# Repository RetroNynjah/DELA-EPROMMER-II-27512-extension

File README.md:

# DELA-EPROMMER-II 27512 Extension

## Background 
This is a reproduction of the 27512 extension board from DELA-Elektronik for the DELA-EPROMMER II for the Commodore 64.  
The user instruction calls this add-on "Umbauset für den DELA-EPROMMER II"

This extension makes it possible to program 27512 EPROMS with the DELA-EPROMMER II by removing VPP from pin 1 and replacing it with the switch controlled address pin A15. A special version of the DELA EPROMMER software is needed which connects VPP to pin 22. This special version is available in the software folder.
The 27512 has to be programmed in two 32kB passes and there are two switches on the board, one for activation/deactivation of the extension and one for 32kB block selection (A15).

When this extension is active, the EPROMMER should only be used with a special version of the DELA EPROMMER software. If the extension is deactivated by the switch, it can be used with the standard software.
A scan of the orginal German user manual for the extension was posted in [this forum thread](https://www.forum64.de/index.php?thread/109845-dela-ii-brenner-mit-zusatzplatine/). There's also a copy in the docs folder.

## Installation instruction
Follow the german user instruction in the docs folder or:

* Remove the diode that is located close to the ZIF socket and the LED. That diode is called D1 on Dirk's reproduction PCB.
* Solder points A,B,C,D on the extensions to the four corner pins of the ZIF socket on the bottom side of the board.
* Wire point E on the extension board to where the anode side of the diode was connected. See photos below or the original instruction in the docs folder.

The part count fort this build is low.
The two slide switches in the design are different from the ones on the original extension because silde switches with that pitch can't be found anymore.  
The ones I used are right-angle switches with a 2mm pitch and has solder connections for the metal frame to add stability. I used a cheap TE switch with part number 1825232-1 which can be found at Digikey with part number A107673-ND.  
The diode is a 1N4148.  
The posts that I use to connect the extension to the pins on bottom of the ZIF-socket are four pins that I pulled out of an IC socket with machined (round) pins. They can usually be grabbed with pliers and pushed out of the socket.

## Usage
**Warning!** Activate the exetension only together with the modified software.

The EPROM has to be programmed in two halved because a full 64kB EPROM image can't fit in RAM so you need to split your ROM file in two halves before programming.

To burn a 27512 EPROM:
* Activate the extension by setting the right switch to the ON position.
* Fire up the custom 512kbit version of the EPROMMER-II application
* Insert EPROM to be programmed.
* Load one half of the 64KByte ROM you want to program.
* Use the left slide switch to select which half you want to program
* Go into the EPROM programming menu and program as usual but select the invisible 6th option (27512) when selecting EPROM type.
* Repeat procedure for the next half of the EPROM

Dirk Wouters has created a reproduction of the complete DELA-EPROMMER II which together with schematics, user manuals and standard software can be found at https://github.com/DL2DW/DELA-EPROMMER-II

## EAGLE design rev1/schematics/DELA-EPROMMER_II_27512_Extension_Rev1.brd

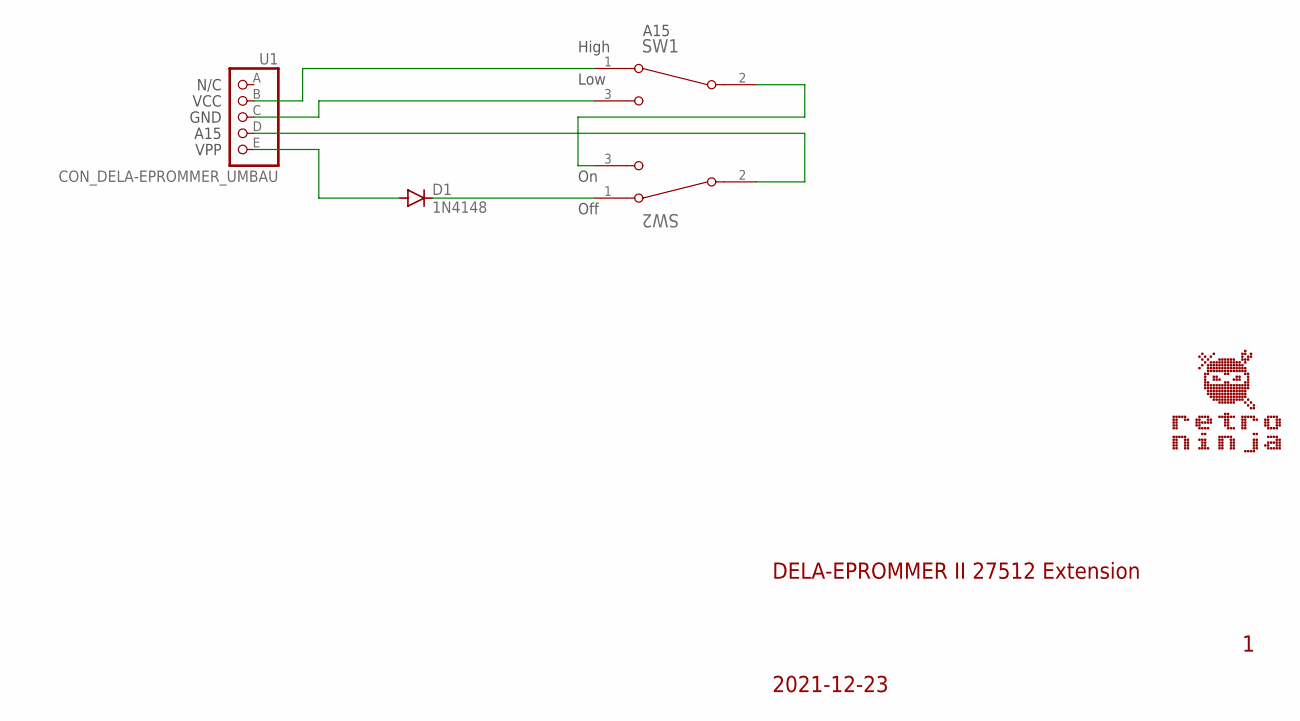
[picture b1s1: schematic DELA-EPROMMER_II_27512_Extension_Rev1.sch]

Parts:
D1: 1N4148; DO35-10
SW1, SW2: SWITCH_SLIDE_2POS_2MM
U1: CON_DELA-EPROMMER_UMBAU

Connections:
unnamed: SW1.1, U1.B
unnamed: SW1.3, U1.C
unnamed: SW2.2, U1.D
unnamed: SW1.2, SW2.3
unnamed: D1.C, SW2.1
unnamed: D1.A, U1.E

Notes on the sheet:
N/C
VCC
GND
A15
VPP
High
Low
Off
2021-12-23
DELA-EPROMMER II 27512 Extension

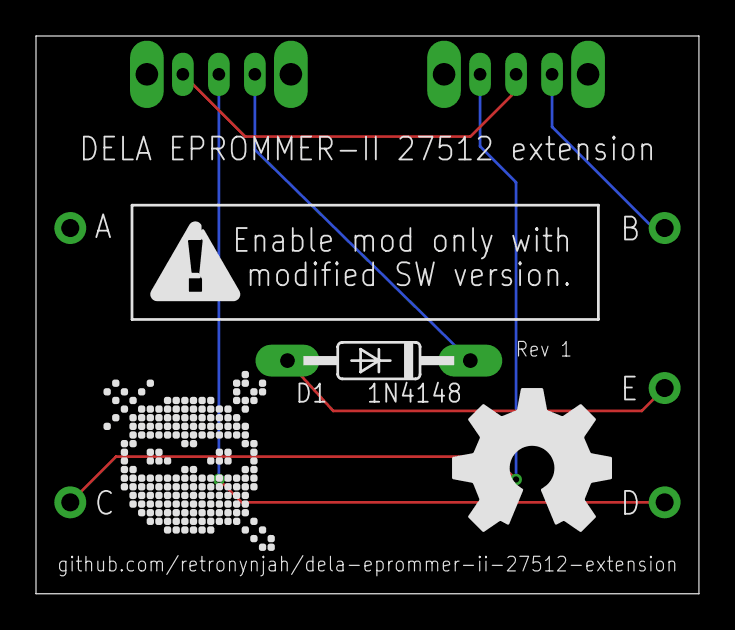
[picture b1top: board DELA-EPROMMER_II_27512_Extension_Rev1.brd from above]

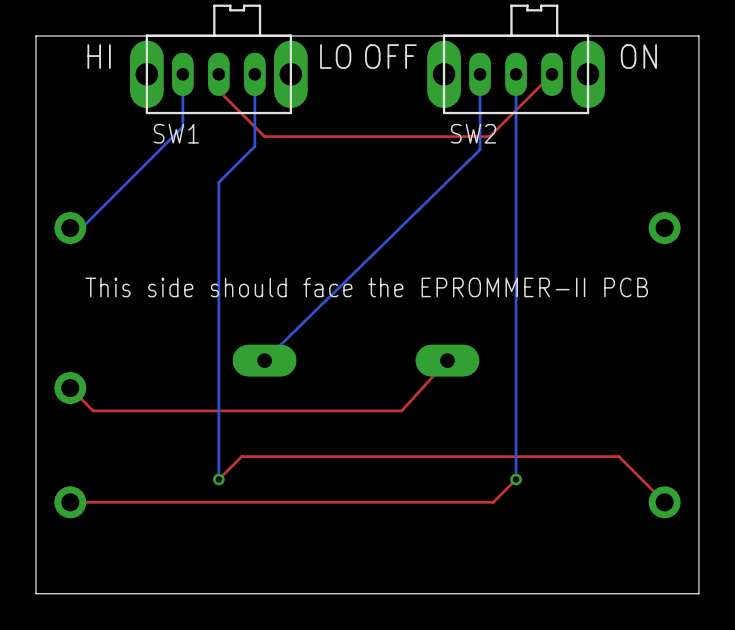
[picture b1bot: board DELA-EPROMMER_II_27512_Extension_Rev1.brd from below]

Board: 2 copper layers, 36.8 x 31.0 mm, 7 parts (2 on the bottom side), 6 nets.

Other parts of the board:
U$1: WARNING_5MM
U$2: RETRONINJA_NOTEXT_10MM
U$3: OSHW_NOTEXT_8MM

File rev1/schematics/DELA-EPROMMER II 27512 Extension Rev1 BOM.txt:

Qty Value                   Device                  Package                 Parts    Description 
1   1N4148                  DIODE_DO35-10           DO35-10                 D1                   
2   SWITCH_SLIDE_2POS_2MM   SWITCH_SLIDE_2POS_2MM   SWITCH_SLIDE_2POS_2MM   SW1, SW2

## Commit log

2022-01-26 First version
2022-01-26 PCB images added
2022-01-26 Schematics
2022-11-29 English software translation
    English version of software provided by giobbino
2022-12-01 Update README.md
    Link to repository
